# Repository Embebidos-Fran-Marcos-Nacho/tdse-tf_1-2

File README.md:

# Dimmer + Switch (Ventilador & Luces)  
Control de ventilador y luces de línea (220 V) desde pared y vía Bluetooth

<div align="center">

**UNIVERSIDAD DE BUENOS AIRES**  
**Facultad de Ingeniería**  
**TA134 – Sistemas Embebidos**  
Curso 1 – Grupo 2

</div>

## Autores
- Ignacio Ezequiel Cavicchioli — Legajo 109428  
- Francisco Javier Moya — Legajo 109899  

---

# 1. Selección del proyecto a implementar

## 1.1 Objetivo del proyecto y resultados esperados

Este proyecto implementa un módulo de control de **ventilador** y **luces de línea (220 V)** que permite operar:

- Desde la pared, por medio de un **botón físico** y un **potenciómetro**  
- Desde un dispositivo móvil mediante **Bluetooth (MIT App Inventor)**

Resultados esperados:

- Control de velocidad del ventilador.  
- Encendido/apagado de luces y ventilador.  
- Feedback mediante **LEDs** y **buzzer** para estados y alertas.  
- Permitir **deshabilitar o configurar el BT** mediante un DIP switch.  
- Guardado en memoria del último estado usado.  
- Funcionamiento seguro sobre cargas de 220 V.

---

## 1.2 Proyectos similares

Para establecer un punto de referencia, se identificaron dos soluciones comerciales que resuelven parcialmente el mismo problema que aborda este proyecto. Ambas están disponibles en el mercado, pero presentan diferencias significativas respecto al sistema que se busca implementar.

1. **Ventilador con control remoto IR/RF**  
   Existen en el mercado local ventiladores controlados por control remoto dedicado. 
   Este tipo de control funciona correctamente, pero presenta limitaciones importantes:
   - Solo tiene control remoto, no tiene control fijo. 
   - No ofrece conectividad con el celular.  
   - No guarda configuraciones ni estados previos del ventilador.  
   - Solo tiene 3 velocidades de ventilador. 

2. **Controladores disponibles internacionalmente (Amazon)**  
   En el mercado internacional existen productos más avanzados, capaces de integrar control de luces y ventilador, conectividad Wi-Fi, y aplicaciones móviles.  
   Sin embargo:
   - Tienen costos significativamente más altos o no cuentan con disponibilidad local inmediata. 
   - En general los que usan wi-fi no tienen tecla y representan una amenaza a la seguridad de la red doméstica del usuario.  

   Estos dispositivos representan lo más cercano al objetivo del proyecto, pero no resultan accesibles para implementarlos o utilizarlos en el contexto local.

En resumen, el proyecto actual se inspira en estas dos líneas de productos, combinando:
- la disponibilidad y simpleza de los controles remotos comerciales locales  
- con la funcionalidad avanzada de los módulos inteligentes que existen internacionalmente  

pero proponiendo una solución **propia, accesible y adaptada al entorno de trabajo de la materia.**

---

## 1.3 Selección de proyecto

La elección del proyecto se fundamenta en una combinación de requerimientos de la consigna, viabilidad técnica y practicidad.

En primer lugar, la cátedra establece como objetivo diseñar un sistema embebido con interacción física y comunicación inalámbrica. Dentro de las alternativas disponibles, el uso de **Bluetooth** se alineó naturalmente con el entorno de desarrollo provisto (MIT App Inventor Companion), permitiendo crear una aplicación funcional sin complejidades de red o protocolos avanzados.

### Razones para no usar Wi-Fi
- Presenta mayor complejidad en configuración, seguridad y mantenimiento de la conexión.  
- Requiere infraestructura adicional (router, red doméstica).  
- Demanda más recursos del microcontrolador.  
- Implica un ciclo de desarrollo más largo, poco compatible con los tiempos del proyecto académico.
- Un dispositivo mal diseñado podría volverse una vulnerabilidad en la red. 

Por ello, Bluetooth resultó ser la opción más equilibrada entre simplicidad, robustez y disponibilidad de herramientas.

### Comparación frente a otras alternativas
- **Control manual únicamente:** No cumple con los requisitos de conectividad inalámbrica definidos por la materia.  
- **Controles RF dedicados:** Los módulos de control remoto comercialmente disponibles para plataformas como Arduino son convenientes para el usuario final, pero no ofrecen un entorno de desarrollo ni la flexibilidad pedagógica necesaria.  
- **Soluciones comerciales completas:** No permiten aprendizaje, programación ni adaptación; además, suelen tener costos elevados o disponibilidad limitada.

### Consideración personal / diseño ideal
En un escenario de producto comercial real, probablemente sería más cómodo utilizar un control **RF dedicado**, especialmente para el uso nocturno (por ejemplo, tener un control en la mesa de luz).  
Sin embargo, dadas las restricciones del proyecto académico y los objetivos de aprendizaje, la elección de Bluetooth y una aplicación móvil resulta la opción más adecuada y formativa.

En conclusión, este proyecto se seleccionó porque:
- cumple con los requerimientos de la materia  
- permite un diseño flexible y completamente programable  
- evita la complejidad innecesaria del Wi-Fi  
- se inspira en productos reales tanto locales como internacionales  
- y aporta una solución integrada para luz + ventilador, que no se encuentra fácilmente en el mercado argentino

---

### 1.3.1 Diagrama en bloques

<div align="center">

</div>

---

# 2. Elicitación de requisitos y casos de uso

## 2.1 Requisitos del proyecto

A continuación se presenta una tabla de requisitos:

### Tabla de requisitos

| Grupo | ID | Descripción |
|-------|-----|-------------|
| Control | 1.1 | El sistema permitirá encender y apagar las **luces** mediante un botón físico. |
|  | 1.2 | El sistema permitirá ajustar la **velocidad del ventilador** mediante un potenciómetro. |
|  | 1.3 | El sistema permitirá controlar el ventilador y las luces vía **Bluetooth**. |
| Bluetooth | 2.1 | El sistema contará con un DIP switch para habilitar o deshabilitar el Bluetooth. |
|  | 2.2 | El DIP switch permitirá seleccionar diferentes **configuraciones o canales** del módulo BT. |
| Indicadores | 3.1 | El sistema contará con **LEDs** que indiquen el estado de conexión del Bluetooth. |
|  | 3.2 | El sistema contará con un **buzzer** para señalizar eventos del Bluetooth. |
| Memoria | 4.1 | El sistema deberá guardar en **memoria flash interna** el último valor de PWM utilizado. |
|  | 4.2 | El sistema deberá restaurar automáticamente el último valor guardado al encender. |
| Seguridad | 5.1 | El sistema deberá operar de forma segura sobre cargas de **220 V**. |
| Aplicación | 6.1 | La aplicación móvil deberá permitir realizar todas las acciones disponibles desde los controles físicos (encendido/apagado de luces y ajuste de velocidad del ventilador). |
|  | 6.2 | El sistema deberá garantizar que el control físico y el control desde la aplicación sean intercambiables: cuando se utilice uno, el otro deberá quedar temporalmente inhabilitado para evitar conflictos de comando. |
---
<!-- |  | 5.2 | El sistema deberá contar con mecanismos de protección ante **sobretemperatura**. | -->

## 2.2 Casos de uso

A continuación se presentan los casos de uso siguiendo el formato del archivo ejemplo.

### Caso de uso 1: Control manual desde la pared

| Elemento | Definición |
|----------|-----------|
| **Disparador** | El usuario presiona el botón físico o ajusta el potenciómetro. |
| **Precondiciones** | El sistema está correctamente alimentado y los módulos están inicializados. |
| **Flujo principal** | El usuario presiona el botón para encender/apagar las luces o gira el potenciómetro para controlar el ventilador. |
---

### Caso de uso 2: Control remoto desde el celular vía Bluetooth

| Elemento | Definición |
|----------|-----------|
| **Disparador** | El usuario abre la aplicación móvil y se conecta al dispositivo mediante Bluetooth. |
| **Precondiciones** | El DIP switch debe habilitar el Bluetooth. El sistema debe estar energizado y en estado operativo. |
| **Flujo principal** | El usuario enciende o apaga las luces y ajusta la velocidad del ventilador desde la aplicación. El sistema recibe los comandos, actualiza el estado interno y modifica las salidas correspondientes. Los indicadores visuales y acústicos reflejan los cambios realizados. |
| **Flujos alternativos** | a) Si el sistema recibe un comando Bluetooth con un **formato inválido**, incompleto o con una estructura distinta a la esperada, el comando se **descarta** y el sistema mantiene el **último estado validado recibido por Bluetooth**.  <br> b) Si durante el funcionamiento se **pierde la conexión Bluetooth**, el sistema conserva el **último estado válido recibido** antes de la desconexión, sin restaurar el modo manual ni cambiar de fuente de control. <br> c) Si el Bluetooth está apagado por DIP switch al intentar conectar, la aplicación no podrá interactuar con el dispositivo. |

### Caso de uso 3: Restauración del último estado guardado

| Elemento | Definición |
|----------|-----------|
| **Disparador** | El sistema se energiza o se reinicia. |
| **Precondiciones** | Debe existir al menos un valor previo guardado en memoria. |
| **Flujo principal** | El sistema lee la memoria flash interna y restaura el último valor de PWM utilizado antes del apagado. El ventilador y/o las luces vuelven al estado correspondiente a ese valor. La aplicación móvil, si se conecta, puede consultar o sincronizar este estado restaurado. |
| **Flujos alternativos** | a) Si la memoria está **vacía**, contiene un valor **inválido**, o los datos resultan **corruptos**, el sistema descarta la lectura y utiliza un **preset de seguridad** en el que tanto las luces como el ventilador permanecen **apagados**. <br> b) Si la memoria resulta **inaccesible** por falla interna, el sistema también entra en el estado seguro con todo apagado, operando únicamente bajo comandos manuales o Bluetooth posteriores. |

---

# 3. Descripción general del sistema

## 3.1 Funcionalidades principales

- Control manual mediante botón y potenciómetro.  
- Control remoto vía Bluetooth.  
- Indicadores LED y buzzer para estados del sistema y del Bluetooth.  
- Memoria interna para restaurar el estado previo.  
- DIP Switch para configurar o deshabilitar el Bluetooth.  
- Operación segura sobre línea de 220 V.

---

# 4. Uso del sistema

## 4.1 Uso manual desde la pared

- Botón físico → encendido/apagado de luces.  
- Potenciómetro → ajuste de velocidad del ventilador.  
- LEDs indican estado del Bluetooth.  

## 4.2 Control desde la app

- Conectarse vía Bluetooth.  
- Encender/apagar luces y ventilador.  
- Ajustar nivel PWM.  
- La app puede mostrar el último valor de PWM restaurado automáticamente.

## 4.3 Telemetría Bluetooth (STM32 -> App)

- El firmware envía un frame binario fijo de **2 bytes** por USART1 (HC-06).
- Formato del frame:
  - Byte 0: `adc_percent` (valor `0..100`).
  - Byte 1: `light_enabled` (`0` = luz apagada, `1` = luz encendida).
- Los bytes se envían en ese orden, sin JSON y sin separadores de texto.
- Para MIT App Inventor, se recomienda leer exactamente 2 bytes por muestra y parsearlos como enteros sin signo de 8 bits.

---

# 5. Configuración (DIP switch)

- **DIP1:** Habilitar o deshabilitar Bluetooth.  
- **DIP2–DIP4:** Configuración del canal o modo del módulo BT.

---

# 6. Cronograma estimado

No se prevé la terminación del TP para diciembre.  
El primer avance se presentará entre enero y febrero de 2026.

---

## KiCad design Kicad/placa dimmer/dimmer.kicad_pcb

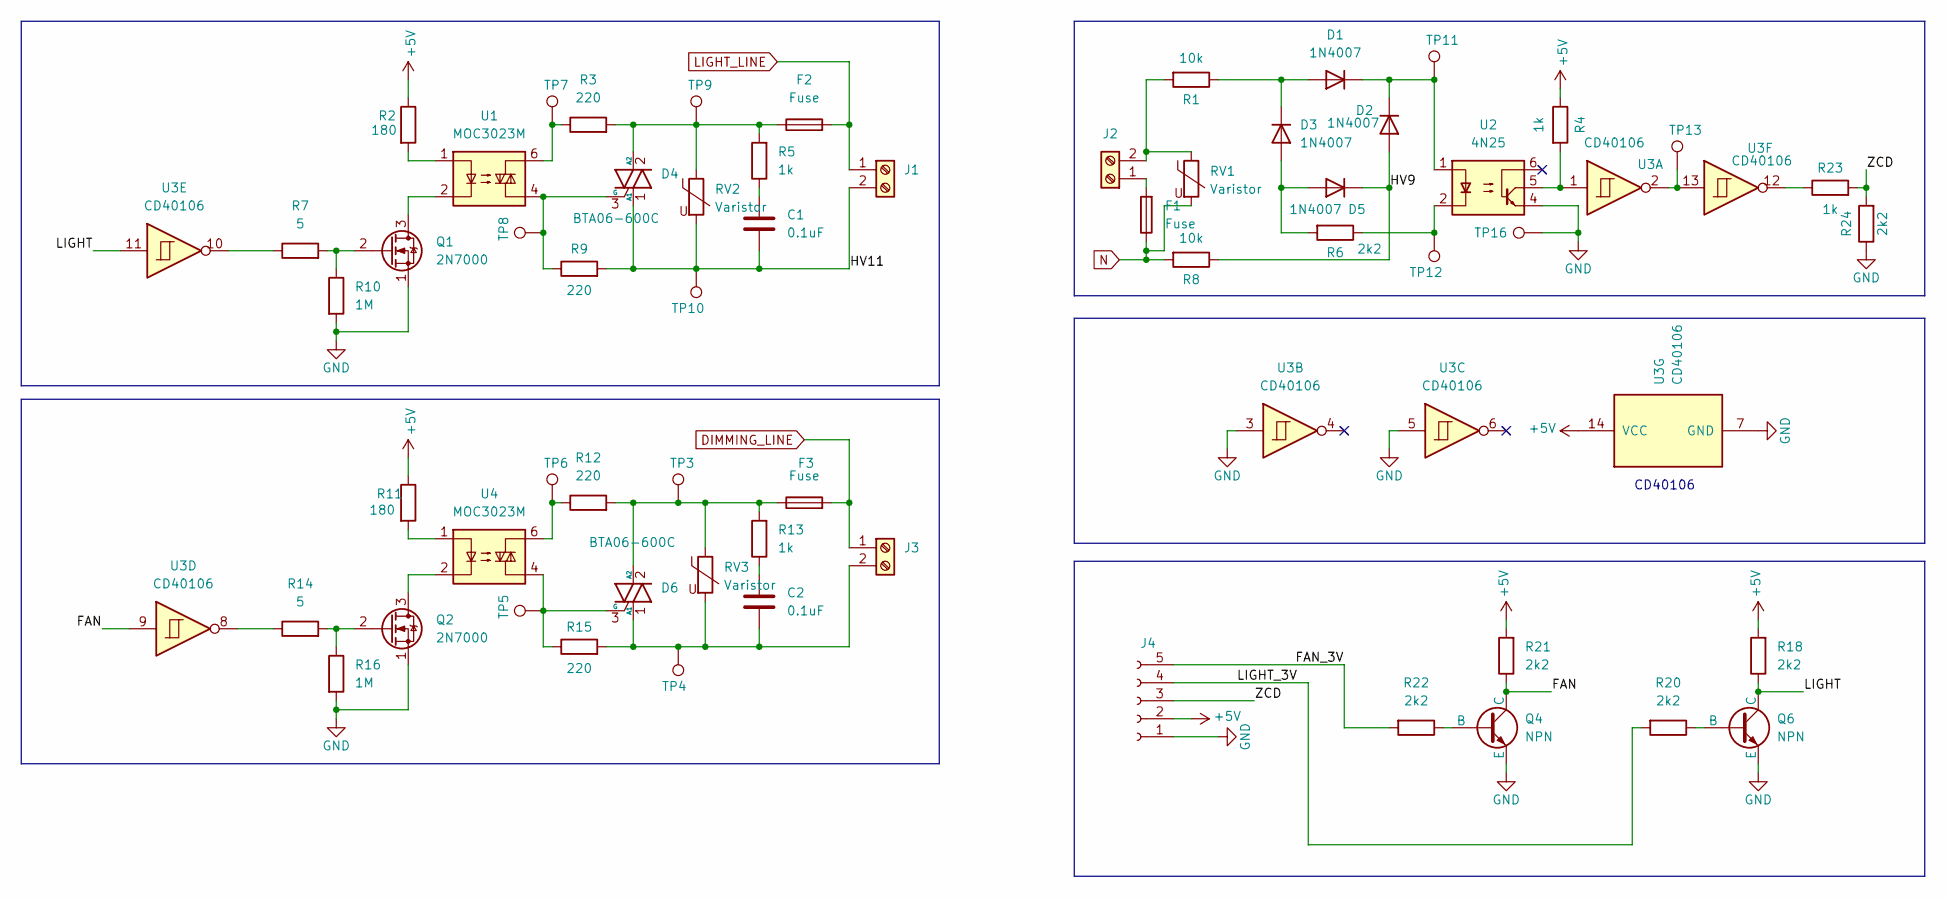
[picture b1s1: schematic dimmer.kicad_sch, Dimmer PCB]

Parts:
C1, C2: 0.1uF; C_Rect_L18.0mm_W9.0mm_P15.00mm_FKS3_FKP3
D1, D2, D3, D5: 1N4007; D_DO-41_SOD81_P10.16mm_Horizontal
D4, D6: BTA06-600C; TO-220-3_Vertical
F1, F2, F3: Fuse; Fuseholder_Clip-5x20mm_Bel_FC-203-22_Lateral_P17.80x5.00mm_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
J1, J2, J3: Screw_Terminal_01x02; TerminalBlock_Phoenix_MKDS-1,5-2-5.08_1x02_P5.08mm_Horizont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
J4: Conn_01x05_Socket; PinHeader_1x05_P2.54mm_Vertical
Q1, Q2: 2N7000; TO-92_Wide
Q4, Q6: NPN; TO-92_Wide
R1, R8: 10k; R_Axial_DIN0516_L15.5mm_D5.0mm_P20.32mm_Horizontal
R2, R11: 180; R_Axial_DIN0204_L3.6mm_D1.6mm_P7.62mm_Horizontal
R3, R9, R12, R15: 220; R_Axial_DIN0204_L3.6mm_D1.6mm_P7.62mm_Horizontal
R4: 1k; R_Axial_DIN0207_L6.3mm_D2.5mm_P7.62mm_Horizontal
R5, R13: 1k; R_Axial_DIN0614_L14.3mm_D5.7mm_P15.24mm_Horizontal
R6, R18, R20, R21, R22, R24: 2k2; R_Axial_DIN0207_L6.3mm_D2.5mm_P7.62mm_Horizontal
R7, R14: 5; R_Axial_DIN0204_L3.6mm_D1.6mm_P7.62mm_Horizontal
R10, R16: 1M; R_Axial_DIN0204_L3.6mm_D1.6mm_P7.62mm_Horizontal
R23: 1k; R_Axial_DIN0207_L6.3mm_D2.5mm_P10.16mm_Horizontal
RV1, RV2, RV3: Varistor; RV_Disc_D15.5mm_W4.2mm_P7.5mm
TP3, TP4, TP5, TP6, TP7, TP8, TP9, TP10, TP11, TP12, TP13, TP16: TestPoint; PinHeader_1x01_P2.54mm_Vertical
U1, U4: MOC3023M; DIP-6_W7.62mm_Socket_LongPads
U2: 4N25; DIP-6_W7.62mm_Socket_LongPads
U3: CD40106; DIP-14_W7.62mm_Socket_LongPads

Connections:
+5V: J4.2, R2.1, R4.1, R11.1, R18.2, R21.2, U3.14 (VCC)
/FAN: Q4.1 (C), R21.1, U3.9
/FAN_3V: J4.5, R22.2
/HV9: D2.2 (A), D5.1 (K), R8.1
/HV11: C1.2, D4.1 (A1), J1.2, R9.2, RV2.2, TP10.1
/LIGHT: Q6.1 (C), R18.1, U3.11
/LIGHT_3V: J4.4, R20.2
/ZCD: J4.3, R23.2, R24.2
DIMMING_LINE: F3.2, J3.1
GND: J4.1, Q1.1 (S), Q2.1 (S), Q4.3 (E), Q6.3 (E), R10.2, R16.2, R24.1, TP16.1, U2.4, U3.3, U3.5, U3.7 (GND)
LIGHT_LINE: F2.2, J1.1
N: F1.1, R8.2, RV1.2
unnamed: C1.1, R5.1
unnamed: C2.1, R13.1
unnamed: D1.2 (A), D3.1 (K), R1.1
unnamed: D1.1 (K), D2.1 (K), TP11.1, U2.1
unnamed: D3.2 (A), D5.2 (A), R6.2
unnamed: D4.2 (A2), F2.1, R3.2, R5.2, RV2.1, TP9.1
unnamed: D4.3 (G), R9.1, TP8.1, U1.4
unnamed: C2.2, D6.1 (A1), J3.2, R15.2, RV3.2, TP4.1
unnamed: D6.2 (A2), F3.1, R12.2, R13.2, RV3.1, TP3.1
unnamed: D6.3 (G), R15.1, TP5.1, U4.4
unnamed: F1.2, J2.1
unnamed: J2.2, R1.2, RV1.1
unnamed: Q1.3 (D), U1.2
unnamed: Q1.2 (G), R7.2, R10.1
unnamed: Q2.3 (D), U4.2
unnamed: Q2.2 (G), R14.2, R16.1
unnamed: Q4.2 (B), R22.1
unnamed: Q6.2 (B), R20.1
unnamed: R2.2, U1.1
unnamed: R3.1, TP7.1, U1.6
unnamed: R4.2, U2.5, U3.1
unnamed: R6.1, TP12.1, U2.2
unnamed: R7.1, U3.10
unnamed: R11.2, U4.1
unnamed: R12.1, TP6.1, U4.6
unnamed: R14.1, U3.8
unnamed: R23.1, U3.12
unnamed: TP13.1, U3.2, U3.13

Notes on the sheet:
CD40106

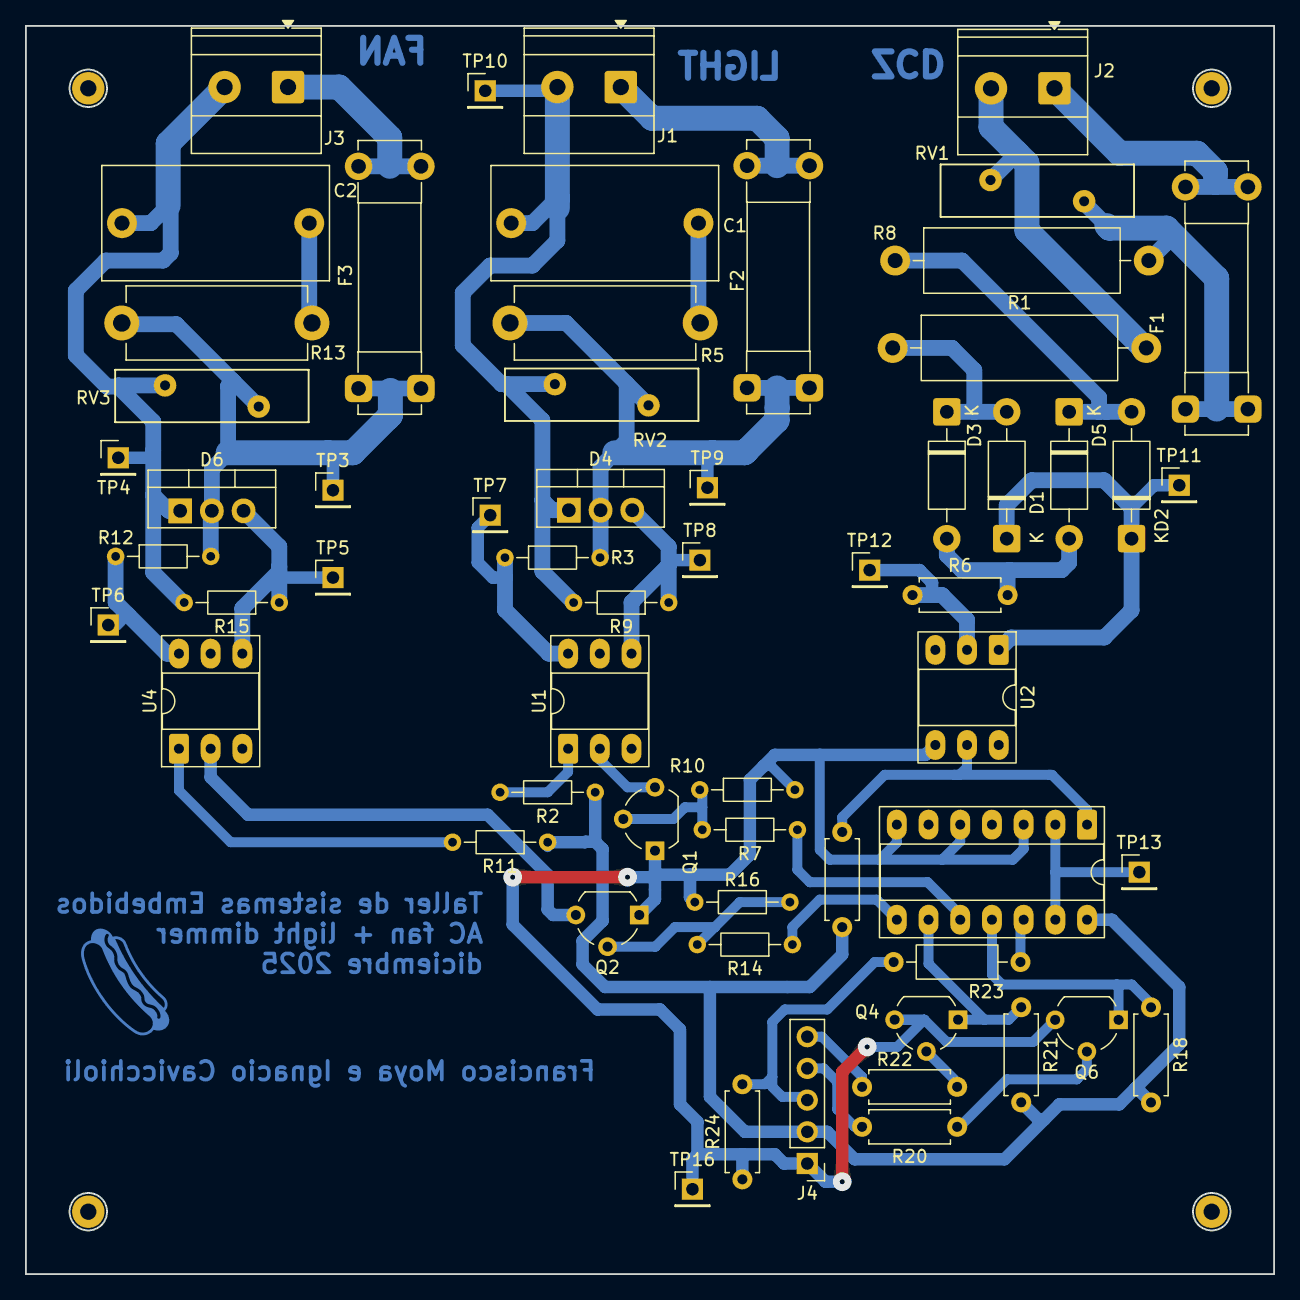
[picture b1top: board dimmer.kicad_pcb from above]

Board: 2 copper layers, 100.0 x 100.0 mm, 60 parts (0 on the bottom side), 40 nets.

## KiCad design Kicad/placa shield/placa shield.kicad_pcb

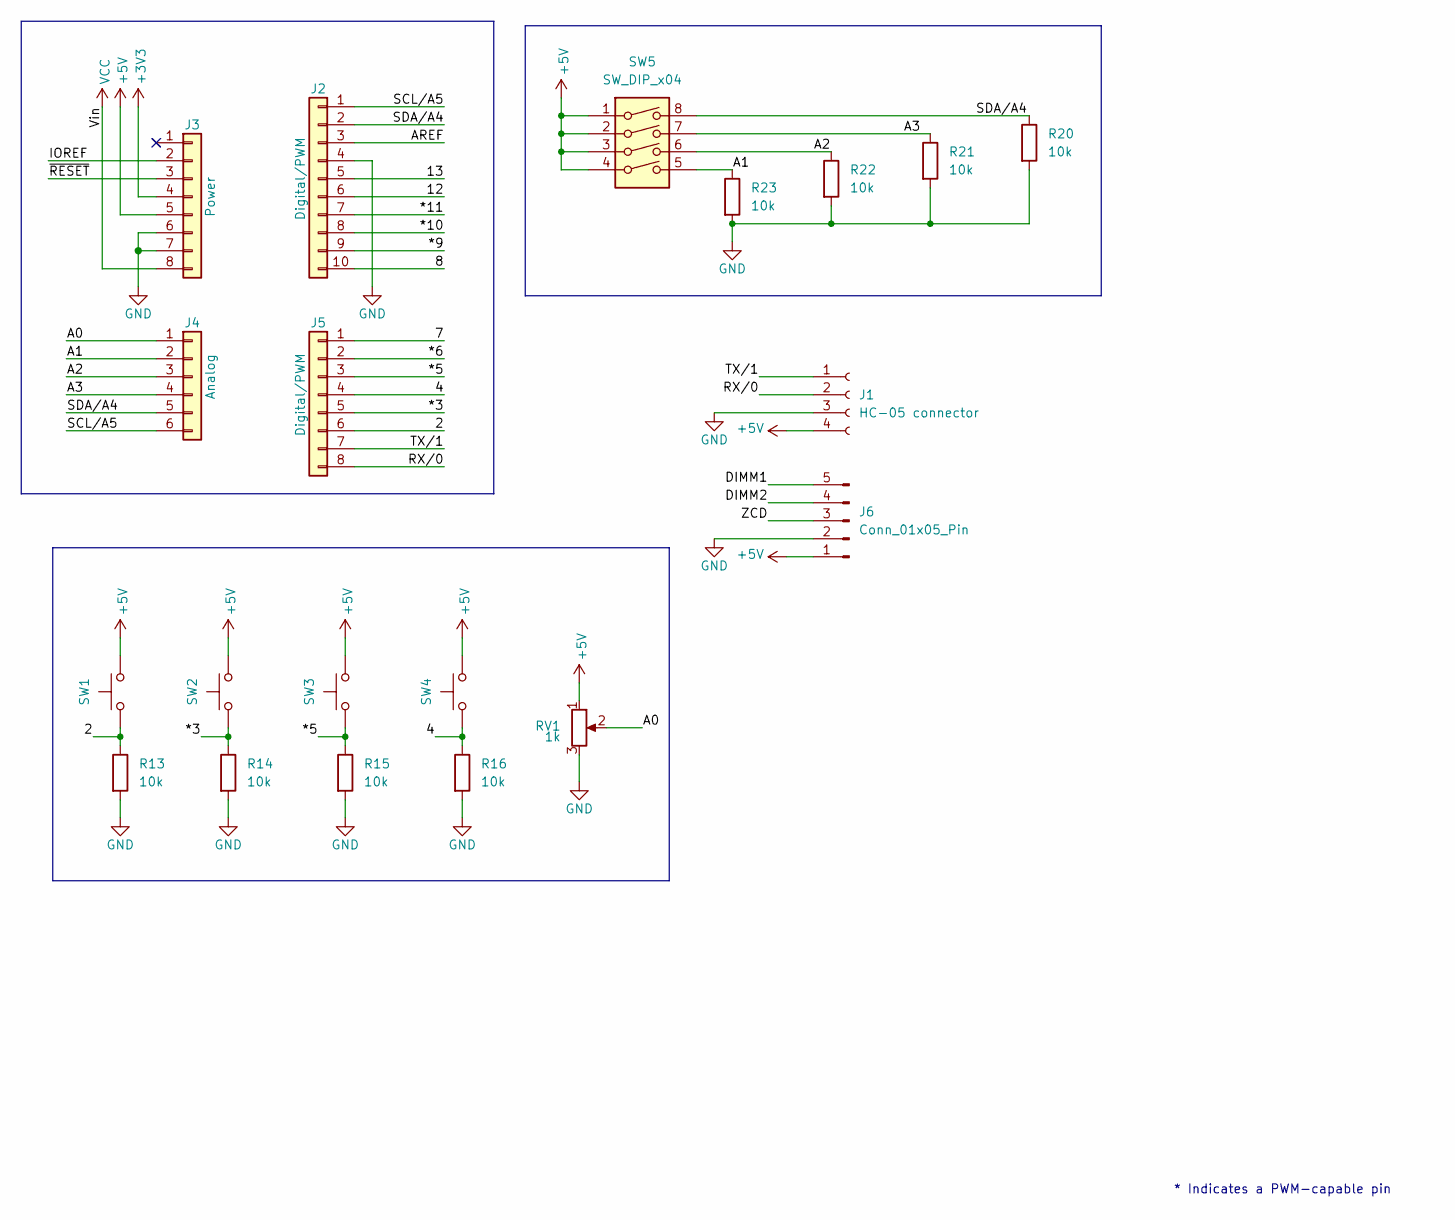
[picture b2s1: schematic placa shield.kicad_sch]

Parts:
J1: HC-05 connector; PinSocket_1x04_P2.54mm_Horizontal
J2: Digital/PWM; PinSocket_1x10_P2.54mm_Vertical
J3: Power; PinSocket_1x08_P2.54mm_Vertical
J4: Analog; PinSocket_1x06_P2.54mm_Vertical
J5: Digital/PWM; PinSocket_1x08_P2.54mm_Vertical
J6: Conn_01x05_Pin; PinHeader_1x05_P2.54mm_Vertical
R13, R14, R15, R16, R20, R21, R22, R23: 10k; R_Axial_DIN0207_L6.3mm_D2.5mm_P7.62mm_Horizontal
RV1: 1k; Potentiometer_Alps_RK163_Single_Horizontal
SW1, SW2, SW3, SW4: SW_Push; SW_PUSH_6mm
SW5: SW_DIP_x04; SW_DIP_SPSTx04_Slide_9.78x12.34mm_W7.62mm_P2.54mm

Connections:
+3V3: J3.4
+5V: J1.4, J3.5, J6.1, RV1.1, SW1.2, SW2.2, SW3.2, SW4.2, SW5.1, SW5.2, SW5.3, SW5.4
/2: J5.6, R13.1, SW1.1
/4: J5.4, R16.1, SW4.1
/7: J5.1
/8: J2.10
/12: J2.6
/13: J2.5
/*3: J5.5, R14.1, SW2.1
/*5: J5.3, R15.1, SW3.1
/*6: J5.2
/*9: J2.9
/*10: J2.8
/*11: J2.7
/A0: J4.1, RV1.2
/A1: J4.2, R23.1, SW5.5
/A2: J4.3, R22.1, SW5.6
/A3: J4.4, R21.1, SW5.7
/AREF: J2.3
/DIMM1: J6.5
/DIMM2: J6.4
/IOREF: J3.2
/RX/0: J1.2, J5.8
/SCL/A5: J2.1, J4.6
/SDA/A4: J2.2, J4.5, R20.1, SW5.8
/TX/1: J1.1, J5.7
/ZCD: J6.3
/~RESET: J3.3
GND: J1.3, J2.4, J3.6, J3.7, J6.2, R13.2, R14.2, R15.2, R16.2, R20.2, R21.2, R22.2, R23.2, RV1.3
VCC: J3.8

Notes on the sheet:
* Indicates a PWM-capable pin

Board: 2 copper layers, 20 parts (4 on the bottom side), 14 nets, no tracks yet.

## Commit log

2025-11-12 Archivos importantes
2025-11-18 Update README with image and formatting changes
    Added an image to the README and improved formatting.
2025-11-18 Fix formatting in README.md
2025-11-18 Revise README for clarity and author information
    Updated README with author names and project description.
2025-11-18 Fix typo in 'Autores' section of README
2025-11-18 Improve README layout and center alignment
    Updated README formatting and alignment.
2025-11-18 diag en bloques
2025-11-18 updated image
2025-11-19 Fix formatting in README.md
    Removed extra newline before the 'Descripción' section.
2025-11-20 placa
2025-12-02 Revise use case details in README.md
    Updated use case descriptions and added details for manual control and Bluetooth handling.
2025-12-04 Harel: Primer commit
2025-12-04 placa y notas de aplicación
2025-12-04 remove hardware from sftware branch
2025-12-04 added prev work to hardware branch
2025-12-04 moved files
    arreglé tema de kicad
2025-12-05 shield arrancado
    Faltaría rutear y ver si podemos hacer algo para fabricarlo nosotros o si o si va a tener que ser doble faz. Sería interesante probar fabricar en china.
2025-12-05 placa 220
2025-12-09 memoria técnica
2025-12-09 shield acomodado
2025-12-11 simuklaciones ltspice y ajustes antes de comprar comps
2025-12-13 consulta Fede
2025-12-14 placa v2
2025-12-14 placa v2 +
2025-12-17 placa terminada
2025-12-28 avances placa
2025-12-28 ajustes finales
    verificación de simulación con LTSpice, cambio de planos.
2025-12-28 eliminar backups viejos
2026-01-02 arreglos
    arreglos comentados en el pull request
2026-01-02 start of shield
2026-01-02 shield
2026-01-06 Continuando con esto
2026-01-21 previo a fabricación
2026-01-21 doc inicial
2026-01-23 Images
2026-01-25 Informe de avances terminado
2026-01-25 Cambios de nombre
2026-01-25 correción de typos
2026-01-26 fotos de ZCD y fab para memoria técnica
    Se hicieron las pruebas con 24 VAC (y modificaciones para que funcione con 24 VAC). Funciona, se pasa a soldar y probar triacs.
2026-01-28 Modify image tag in Informe_de_Avances.md
    Updated image tag in Informe_de_Avances.md to remove height attribute.
2026-01-30 Revise STATECHART_EXPLANATION.md for clarity
    Updated the document to improve clarity and consistency in terminology.
2026-02-03 Video de funcionamiento del hardware - prueba con arduino mínimo
2026-02-03 correcion imágenes
2026-02-03 imagenes renombradas
2026-02-03 deprecated 3D files - gabinete
2026-02-05 inicio de software a partir de plantilla de cursada y pinout
2026-02-07 inicio de etapa final
    preparando repo para agentes
2026-02-07 cambios en .ioc
2026-02-07 moved pinout
2026-02-08 pinout final definition
2026-02-08 esquema shield actualizado con ínout final
2026-02-09 programación
2026-02-10 modo prueba
2026-02-10 eliminar semiloger
2026-02-10 more logger shenannigans
2026-02-10 test mode
2026-02-10 toques extras
2026-02-10 modo prueba 2
2026-02-11 cambios para bluetooth, falta baudrate
2026-02-11 sketch arduino
2026-02-11 pulido BL
2026-02-11 volumen buzzer y fault mode
2026-02-14 conexionado
2026-02-14 modo prueba apagado en configs
2026-02-14 varios
2026-02-14 buzzer
2026-02-14 agregado de timers para arreglar timings
2026-02-14 cambios
2026-02-14 mas correciones
2026-02-14 mas arreglos
2026-02-15 adc simplificado y arreglo buzzer
2026-02-15 regreso a adc simple, BT cambiado
2026-02-17 ajustes hardware
    renombrar carpeta kicad -> hardware y anotaciones planos
2026-02-17 cambio bluetooth
    ahora el bluetooth envia 3 bytes en vez de un json entero. esto es más facil de decodificar en la app
2026-02-17 app celular terminada
    se sube apk y proyecto de mit app inventor
2026-02-17 Actualización de la memoria técnica
2026-02-17 código prueba stm32
2026-02-17 arreglo app
2026-02-17 build console & analyzer
2026-02-17 Update section numbers and add images in documentation
2026-02-17 Update in memoria tecnica
2026-02-17 wcet
2026-02-17 wcet listo, falta consumo
2026-02-17 console
2026-02-17 consumo
2026-02-17 fotos hardware
2026-02-17 imgs
2026-02-17 toques finales
2026-02-18 memo
2026-02-18 final
2026-02-18 Update design note reference in Memoria técnica.md
    Clarified the source of the design notes in the document.
2026-02-18 Clarify voltage description for Schmitt triggers
    Updated text to clarify that the voltage reached the threshold for triggering Schmitt triggers.
2026-02-18 state init
2026-02-18 Rename State Init1.png to State Init.png
2026-02-19 creacion de documento de latex e inicio de correcciones
    hasta acá no son las imágenes
2026-02-19 índice
2026-02-19 captions y hilado de imágenes en texto
2026-02-19 imagenes en buen tamaño y embeded video
2026-02-19 links web
2026-02-19 eliminar 2 bytes
2026-02-19 linebreaks
2026-02-19 Fix formatting and add line breaks in documentation
    agregué <br><br> a mano despues de todas las imagens
2026-02-19 referencia a tablas
2026-02-19 arreglo de italica para captions
2026-02-19 Update technical documentation with module and hardware details
    Added details about system modules and hardware design.
2026-02-19 Update image link for ZCD simulation in documentation
2026-02-19 Standardize formatting in consumption measurement section
    sería los cambios de 3.3 a 3,3 y dejando un espacio entre el número y la unidad.
2026-02-19 Ajustes finales previos a re-lectura y re-entrega
2026-02-19 Update version log with detailed correction notes
2026-02-19 Fix formatting and update section titles in documentation
2026-02-19 Update section titles in technical documentation
2026-02-19 Actualización de las imágenes del Diagrama de Harel
2026-02-19 Update Memoria técnica.md
    Updated image source for the statechart in the technical documentation.
2026-02-19 Fix image references in Memoria técnica.md
    Updated image references for statecharts and states in the technical documentation.
2026-02-19 Adjust image sizes in Memoria técnica.md
2026-02-19 Add description and images for initialization states
2026-02-19 Fix typos and improve text clarity in documentation
2026-02-19 Update table header formatting in technical document
2026-02-19 Revise table header format and add typo correction support
    Updated table headers for clarity and added typo correction support.
2026-02-20 cambios de carátula, mover logo arriba
2026-02-20 ajuste centrado carátula
2026-02-20 que el link se vea más claro
2026-02-20 Correct capitalization of 'Wi-Fi' throughout document
2026-02-20 Fix capitalization of 'Wi-Fi' throughout document
    ahora es Wi-Fi, no WI-FI
2026-02-20 Fix formatting and punctuation in requirements table
2026-02-20 requisitos cambiados indicados con número
    Clarified the summary of requirement changes and specified affected requirements.
2026-02-20 Update links and clarify requirements section
2026-02-20 agrego entrada en tabla de revisión
